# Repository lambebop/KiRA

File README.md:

# KiRA Flight Computer

Flight computer of Karlsruhe International Rocketry Association

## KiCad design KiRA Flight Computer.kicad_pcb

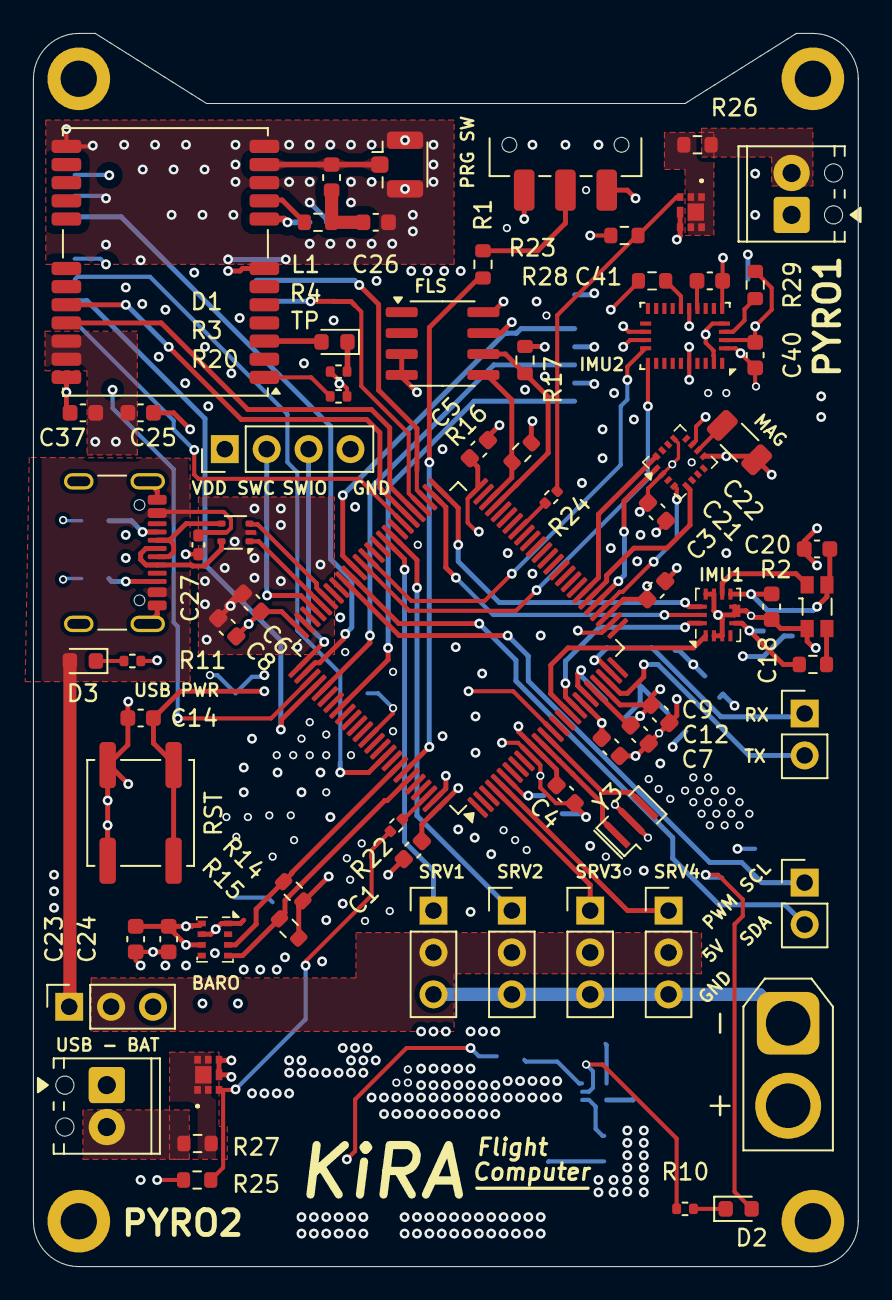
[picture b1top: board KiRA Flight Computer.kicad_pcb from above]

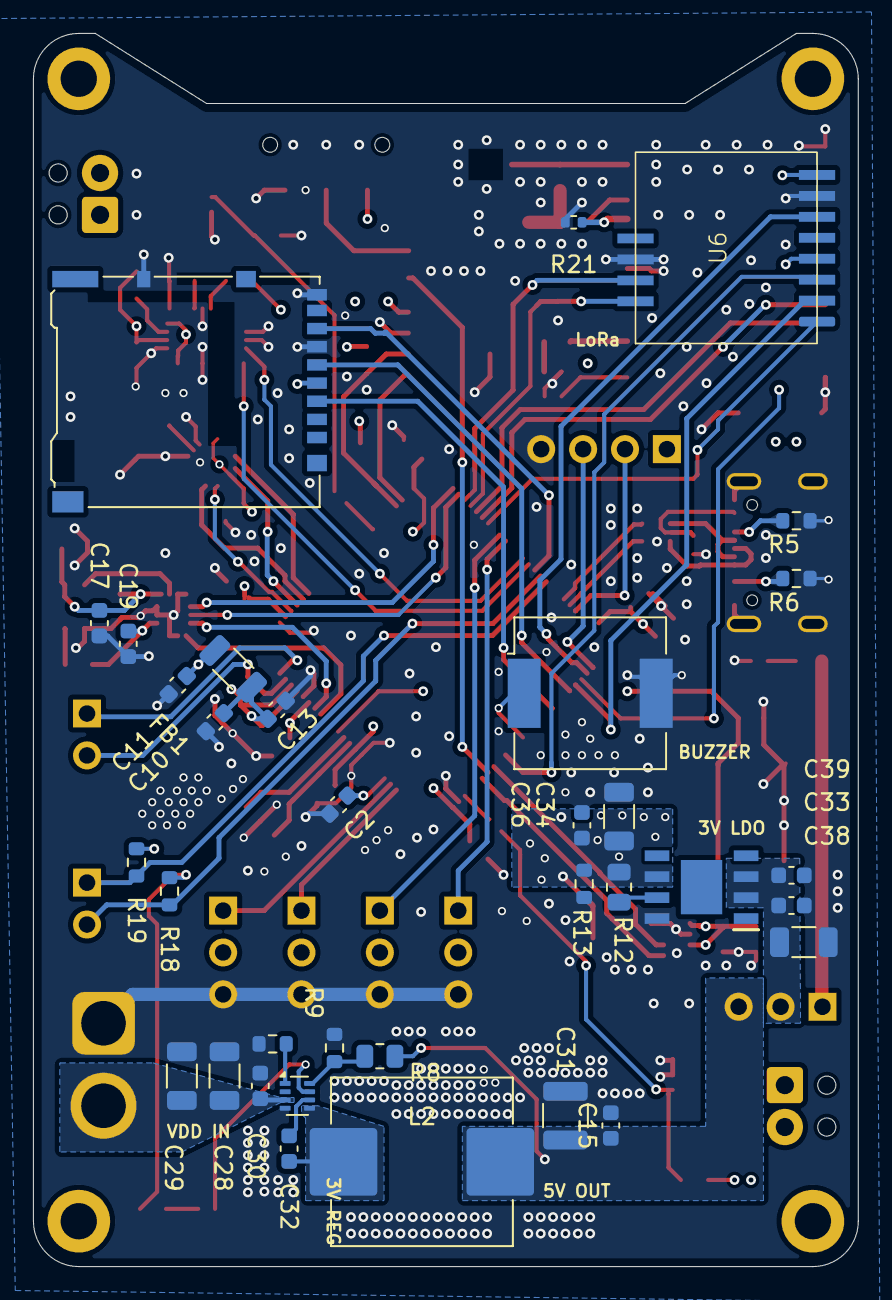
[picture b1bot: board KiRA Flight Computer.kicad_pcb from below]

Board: 4 copper layers, 50.0 x 74.8 mm, 110 parts (34 on the bottom side), 84 nets.

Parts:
BZ1: Buzzer; Buzzer_CUI_CPT-9019S-SMT
C1, C2, C3, C4, C5, C6, C7, C9, C12, C14, C15, C18, C20, C23, C24, C25, C26, C30, C32, C36, C39, C40, C41: 100nF; C_0603_1608Metric
C8, C11, C33: 4.7uF; C_0603_1608Metric
C10, C13, C21, C37: 1uF; C_0603_1608Metric
C17: 2.2uF; C_0603_1608Metric
C19: 10nF; C_0603_1608Metric
C22, C28, C29, C34, C38: 10uF; C_1206_3216Metric
C27: 100nF; C_0402_1005Metric_Pad0.74x0.62mm_HandSolder
C31: 47uF; C_1210_3225Metric
D1, D3: LED_GREEN; LED_0603_1608Metric
D2: LED_RED; LED_0603_1608Metric
FB1: 120R; L_1206_3216Metric
H1, H2, H3, H4: MountingHole; MountingHole_2.2mm_M2_DIN965_Pad
IC1: SC4216HSETRT; SOIC127P600X175-9N
J1: Conn_01x04_Pin; PinHeader_1x04_P2.54mm_Vertical
J2: USB_C_Receptacle_USB2.0_14P; USB_C_Receptacle_GCT_USB4105-xx-A_16P_TopMnt_Horizontal
J3, J9, J11, J12: Conn_01x03_Pin; PinHeader_1x03_P2.54mm_Vertical
J4: Conn_01x03; PinSocket_1x03_P2.54mm_Vertical
J5: Conn_01x02; AMASS_XT30U-F_1x02_P5.0mm_Vertical
J6: Micro_SD_Card_Det1; microSD_HC_Hirose_DM3AT-SF-PEJM5
J8, J10: Conn_01x02_Pin; PinHeader_1x02_P2.54mm_Vertical
J13, J14: Screw_Terminal_01x02; TerminalBlock_Phoenix_MPT-0,5-2-2.54_1x02_P2.54mm_Horizontal
J15: Conn_Coaxial; U.FL_Hirose_U.FL-R-SMT-1_Vertical
L1: 27nH >300mA; L_0603_1608Metric
L2: 7.8uH; L_APV_APH1050
Q1, Q2: FDMA430NZ
R1, R2, R13, R28, R29: 10k; R_0603_1608Metric
R3, R10, R11, R22, R24: 220R; R_0402_1005Metric
R4: 10R; R_0603_1608Metric
R5, R6: 5.1k; R_0603_1608Metric
R7: 0R; R_0603_1608Metric
R8, R12: 56k; R_0805_2012Metric
R9: 11k; R_0603_1608Metric
R14, R15, R16, R17, R18, R19, R23, R25: 4.7k; R_0603_1608Metric
R20, R21: R; R_0402_1005Metric
R26, R27: 1R; R_0603_1608Metric
SW1: SW_Push; SW_Push_1P1T_NO_CK_KSC6xxJ
SW2: SW_SPDT; SW_SPDT_CK_JS102011SAQN
U1: ICM-426788P; Bosch_LGA-14_3x2.5mm_P0.5mm
U2: STM32F407VGTx; LQFP-100_14x14mm_P0.5mm
U3: MMC5883MA; LGA-16_3x3mm_P0.5mm
U4: DPS368; Bosch_LGA-8_2x2.5mm_P0.65mm_ClockwisePinNumbering
U5: NEO-M9N; ublox_NEO
U6: Wio-SX1262; WIO SX1262
U7: USBLC6-2P6; SOT-666
U8: TPS62933P; SOT-583-8
U9: Tudi AT24CM02-SSHD-T-TUDI; SOIC-8_3.9x4.9mm_P1.27mm
U10: BNO055; LGA-28_5.2x3.8mm_P0.5mm
Y2: OV_7604; Oscillator_SMD_SeikoEpson_SG3030CM
Y3: Resonator; Resonator_SMD_Murata_CSTxExxV-3Pin_3.0x1.1mm

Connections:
+3.3V: C1.1, C2.1, C3.1, C4.1, C5.1, C6.1, C7.1, C8.1, C11.1, C17.1, C18.1, C19.1, C20.1, C21.1, C23.1, C24.1, C25.1, C34.1, C36.1, C37.1, C40.1, D2.2 (A), FB1.2, IC1.6 (VO), J1.1, J6.4 (VDD), R2.1, R12.2, R13.1, R14.1, R15.1, R16.1, R17.1, R18.1, R19.1, R28.1, R29.1, SW2.3 (C), U1.5 (VDDIO), U1.8 (VDD), U2.6 (VBAT), U2.11 (VDD), U2.19 (VDD), U2.28 (VDD), U2.50 (VDD), U2.75 (VDD), U2.100 (VDD), U3.2 (VDD), U3.13 (VDDIO), U4.6 (VDDIO), U4.8 (VDD), U5.22 (V_BCKP), U5.23 (VCC), U6.8 (VCC), U9.8 (VCC), U10.3 (VDD), U10.5 (PS1), U10.28 (VDDIO), Y2.4 (Vcc)
+5V: C33.1, C38.1, C39.1, IC1.2 (EN), IC1.3 (VIN), J3.2, J4.2, J9.2, J11.2, J12.2
+BAT: C28.1, C29.1, C30.1, J5.2, J13.1, J14.1, U8.3 (VIN)
+V_REG: C15.1, C31.1, J4.3, L2.2, R8.1
/BOOT0: R1.2, U2.94 (BOOT0)
/DP+: U2.71 (PA12), U7.1 (I/O1)
/DP-: U2.70 (PA11), U7.3 (I/O2)
/IMUs/MPU_CLK: U1.9 (INT2/CLK), Y2.1 (CLK)
/NRST: C14.1, SW1.2, U2.14 (NRST)
/Pinout/PYOUT1: Q1.1 (D_1), Q1.2 (D_2), Q1.5 (D_3), Q1.6 (D_4), Q1.7 (D_5), R26.2
/Pinout/PYOUT2: Q2.1 (D_1), Q2.2 (D_2), Q2.5 (D_3), Q2.6 (D_4), Q2.7 (D_5), R27.2
/SWCLK: J1.2, U2.72 (PA13)
/SWIO: J1.3, U2.76 (PA14)
BUSY: U2.53 (PB14), U6.11 (BUSY)
BUZZER: BZ1.1 (+), U2.88 (PD7)
DIO1: U2.54 (PB15), U6.12 (DIO1)
GND: BZ1.2 (-), C1.2, C2.2, C3.2, C4.2, C5.2, C6.2, C7.2, C8.2, C9.2, C10.2, C11.2, C12.2, C13.2, C14.2, C15.2, C17.2, C18.2, C19.2, C20.2, C21.2, C22.2, C23.2, C24.2, C25.2, C26.2, C27.1, C28.2, C29.2, C30.2, C31.2, C33.2, C34.2, C36.2, C37.2, C38.2, C39.2, C40.2, C41.2, IC1.8 (GND), J1.4, J2.A1 (GND), J2.A12 (GND), J2.B1 (GND), J2.B12 (GND), J2.S1 (SHIELD), J3.3, J5.1, J6.6 (VSS), J6.9 (DET), J6.10 (SHIELD), J9.3, J11.3, J12.3, J15.2 (Ext), Q1.4 (S_1), Q1.8 (S_2), Q2.4 (S_1), Q2.8 (S_2), R3.2, R5.1, R6.1, R7.2, R9.2, R11.2, R13.2, R20.2, R21.2, R23.2, R25.2, SW1.1, SW2.1 (A), U1.2 (RESV), U1.3 (RESV), U1.6 (GND), U1.7 (RESV), U1.10 (RESV), U1.11 (RESV), U2.10 (VSS), U2.20 (VSSA), U2.27 (VSS), U2.74 (VSS), U2.99 (VSS), U3.9 (GND), U3.11 (GND), U4.1 (GND), U4.7 (GND), U5.7 (VDD_USB), U5.10 (GND), U5.12 (GND), U5.13 (GND), U5.24 (GND), U6.7 (GND1), U6.10 (GND2), U7.2 (GND), U8.4 (GND), U9.3 (A2), U9.4 (GND), U9.7 (WP), U10.2 (GND), U10.6 (PS0), U10.10 (BL_IND), U10.17 (COM3), U10.18 (COM2), U10.25 (GNDIO), Y2.2 (GND), Y3.2
I2C1_SCL: R15.2, U2.95 (PB8), U4.4 (SCK)
I2C1_SDA: R14.2, U2.93 (PB7), U4.3 (SDI)
I2C2_SCK: R17.2, U2.47 (PB10), U9.6 (SCL)
I2C2_SDA: R16.2, U2.48 (PB11), U9.5 (SDA)
I2C3_SCL: J8.1, R19.2, U2.67 (PA8)
I2C3_SDA: J8.2, R18.2, U2.66 (PC9)
unnamed: C26.1, L1.1, R4.2
unnamed: D1.2 (A), U5.3 (TIMEPULSE)
unnamed: D1.1 (K), R3.1
unnamed: D2.1 (K), R10.2
unnamed: D3.1 (K), R11.1
unnamed: IC1.7 (FB), R12.1
unnamed: J2.A5 (CC1), R5.2
unnamed: J2.B5 (CC2), R6.2
unnamed: J2.A6 (D+), J2.B6 (D+), U7.6 (I/O1)
unnamed: J2.A7 (D-), J2.B7 (D-), U7.4 (I/O2)
unnamed: J13.2, R26.1
unnamed: J14.2, R27.1
unnamed: J15.1 (In), L1.2, U5.11 (RF_IN)
unnamed: Q1.3 (G), R23.1, R24.2
unnamed: Q2.3 (G), R22.2, R25.1
unnamed: R1.1, SW2.2 (B)
unnamed: C22.1, U3.10 (CAP)
unnamed: R4.1, U5.9 (VCC_RF)
unnamed: R21.1, U5.8 (~RESET)
unnamed: R20.1, U5.1 (~SAFEBOOT)
unnamed: C32.1, U8.6 (BST)
unnamed: R8.2, R9.1, U8.8 (FB)
unnamed: R10.1, U8.7 (PG)
unnamed: R7.1, U8.1 (RT)
unnamed: C32.2, L2.1, U8.5 (SW)
unnamed: C41.1, U10.9 (CAP)
unnamed: R29.2, U10.4 (~BOOT_LOAD_PIN)
unnamed: R28.2, U10.11 (~RESET)
unnamed: R2.2, Y2.3 (OE)
PWM1: J3.1, U2.60 (PD13)
PWM2: J9.1, U2.59 (PD12)
PWM3: J11.1, U2.4 (PE5)
PWM4: J12.1, U2.5 (PE6)
PY1: R24.1, U2.43 (PE12)
PY2: R22.1, U2.98 (PE1)
RCC IN: U2.12 (PH0), Y3.1
RCC OUT: U2.13 (PH1), Y3.3
RF_SW1: U2.57 (PD10), U6.1 (RF_SW1)
RX: U2.63 (PC6), U10.19 (COM1)
SDIO_CK: J6.5 (CLK), U2.80 (PC12)
SDIO_CMD: J6.3 (CMD), U2.83 (PD2)
SDIO_D0: J6.7 (DAT0), U2.65 (PC8)
SPI1_CS: U2.29 (PA4), U3.4 (SPI_CS)
SPI1_MISO: U2.31 (PA6), U3.5 (SDO)
SPI1_MOSI: U2.32 (PA7), U3.16 (SDA)
SPI1_SCK: U2.30 (PA5), U3.1 (SCL)
SPI2_CS: U1.12 (AP_CS), U2.51 (PB12)
SPI2_MISO: U1.1 (AP_SDO), U2.17 (PC2)
SPI2_MOSI: U1.14 (AP_SDA), U2.18 (PC3)
SPI2_SCK: U1.13 (AP_SCL), U2.52 (PB13)
SPI3_CS: U2.77 (PA15), U6.6 (NSS)
SPI3_MISO: U2.79 (PC11), U6.2 (MISO)
SPI3_MOSI: U2.91 (PB5), U6.3 (MOSI)
SPI3_SCK: U2.78 (PC10), U6.4 (SCK)
TX: U2.64 (PC7), U10.20 (COM0)
UART3_RX: U2.56 (PD9), U5.20 (TXD/SPI_MISO)
UART3_TX: U2.55 (PD8), U5.21 (RXD/SPI_MOSI)
UART4_RX: J10.1, U2.24 (PA1)
UART4_TX: J10.2, U2.23 (PA0)
VBUS: C27.2, D3.2 (A), J2.A4 (VBUS), J2.A9 (VBUS), J2.B4 (VBUS), J2.B9 (VBUS), J4.1, U7.5 (VBUS)
VREF+: C9.1, C10.1, C12.1, C13.1, FB1.1, U2.21 (VREF+), U2.22 (VDDA)

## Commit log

2025-09-21 init
2025-09-21 add sd card reader
2025-09-29 "Update KiRA Flight Computer schematic and PCB files"
2025-09-30 Update PCB
2025-10-05 questionable changes
2025-10-06 PCB Update
2025-10-07 Silkscreen update
2025-10-07 add dep
2025-10-07 Fix
    - Add decoupling cap
    - Component layout
    - Redraw zones
    - New buck converter
    - Layout tweaks
    - Change connector
2025-10-17 Update Formulars
